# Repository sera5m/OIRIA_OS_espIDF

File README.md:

# OIRIA OS (ESP-IDF)

Smartwatch firmware. Dual purpose: a normal smart device, and an industrial or semi-universal controller for whatever hardware it meets — consumer gear, raw modules, or robotics, all in one device.

## what

OIRIA OS is intended to behave like Linux for small devices that have no MMU, without containing any Linux components. It should be friendly enough for a layman and deep enough for an expert, with a clean path between the two. It is also meant to meet high performance criteria for microcontrollers.

The smartlink companion is part of this, given The watch is both a wearable and a controller.

## why

Wear OS is not good enough. Many standard libraries (microGL and the like) do not meet the performance bar. Mixed drivers and manufacturers rarely work together because of side effects, nonstandard management, or nonstandard I/O state machines. A small, owned stack avoids that.

## how

OIRIA OS is broken into state-machine layers with component managers, similar to how modern Linux handles services. Encapsulation is kept thin for performance. There is no user/kernel boundary and no MMU sandbox. Isolation is by convention and by declared capabilities. FreeRTOS sits under everything. Two long-lived managers (WindowManager and appManager) own the frame and the app list. Apps own their windows. Input is handled by asynch events with periodic check. ipc is handled by rshell pipes as a DataItem when it needs to leave an app, or the device itself (best performance with batching; low latency without, but higher overhead)

---

# Main services

**graphics system**

- name: WindowManager (`os_code/core/window_env/MWenv`)
- purpose: display compositor. Owns the window list, z-order, and the frame. Draws windows to the framebuffer and pushes dirty rows to the panel.
- architectural principles: apps build a `Window` and hand it to the manager. The manager borrows; it does not own the content. Dirty flags over full redraws. Double-buffered framebuffer, 45 fps cap. Style and widgets live in `window_env/ui`. DOM pack exists for the second chip; apply-to-LCD is not wired yet.

**desktop environment**

- name: apps + appManager focus
- purpose: the set of things the user sees and switches between (menu, watch face, health, browser, and so on). Focus is a pointer plus a highlight flag plus a layer number.
- architectural principles: an app is not a system object that requests a window. It constructs one. `set_focused_app` raises the window and sets the highlight. The input path delivers events only to the focused app. No desktop shell in the Unix sense — the menu and the focused app are the desktop.

**input system**

- name: input handler (`os_code/middle_layer/input`)
- purpose: turn hardware (encoder knobs, buttons, and later USB HID) into `InputEvent`s and route them.
- architectural principles: one packed event, one queue (`ProcInputQueTarget`). The input task produces; apps consume via `receive_event_input`. No device-node tree. Target enum decides where it goes. Keyboard, mouse, touch, and phone-as-input are not in the path yet.

**application scheduler and system**

- name: rshell (`os_code/core/rShell`)
- purpose: app lifecycle and scheduling on top of FreeRTOS. Registers apps, opens them, starts their task, routes input and pipes, and owns focus.
- architectural principles: `AppBase` is the unit. `start_task` is an `xTaskCreate` of a loop that calls `tick_app` at `tick_rate_hz` and feeds the watchdog. Input arrives on a separate path (`route_input_to_focused`). Pipes and DataItems are the long-term data currency; most apps still talk to their window directly. Capabilities are declared on the manifest (`USES_SD_CARD`, `STREAM_OUT_CAPABLE`, and others) and checked at the call for GPIO, wireless, and wake. The ELF loader is not sandboxed (no mmu) so be careful if developing. further suppoer will be added in the future

**scripting**

- name: Toplethos (`os_code/core/rs_vm`)
- purpose: on-device scripting layer for behavior that does not belong in C++.
- architectural principles: bytecode interpreter (`rsvm_compile` + `rsvm_run`). No JIT on the ESP32-S3. The VM asks the host through function pointers; the host is not a kernel. Desktop AOT and the full language tree live elsewhere, as this device can only handle a small subset of features and will not be able to handle simd, self modifying code, intelegently self modifying code, or high bit width instructions or workloads)
why: bash is too simple. lua slow and big. java too huge and does not allow manual memory access. 

---

**Build:** this repo is the ESP-IDF project. See [BUILD.md](BUILD.md).

```bash
. ~/esp/esp-idf/export.sh
git clone https://github.com/sera5m/OIRIA_OS_espIDF
cd OIRIA_OS_espIDF
idf.py build
idf.py -p /dev/ttyACM0 flash monitor

```
**developing apps for this device**
app development is still experimental and desktop-only. support coming to the mobile app sometime in the future. please test all of your apps features before submitting it to the repo [HERE](https://github.com/sera5m/oiria-index)

**SMARTLINK APP**
[MOBILE, ANDROID](https://github.com/sera5m/android_smartlink_app)
[mobile, apple] (lol)
[DESKTOP, LINUX,arch x86] (NOT DONE) 
[DESKTOP, LINUX, deb] (not done)
[DESKTOP, microslop windows] (not done)

**LIABILITY WARNING**
this device is still experimental and may not perform exactly as indented, this being an inherent limitation of software. while the creators of this software have taken all caution to maintain legality and safety in features, this device is a tool, and as with all tools, misuse is possible. ensure that the electronics toolkit, universal remote, or quick utils are used only on devices that you have ownership of

**WARNING**

This device uses a custom programming language named **Toplethos** as a scripting layer, for more detailed behavior and edge programming than bash or Lua. It is a C++/Rust-like language with several features inspired by Lisp. It can be interpreted (full support for a RISC-like 32-bit subset) and compiled on device (support incomplete — file bug reports, as unexpected behavior will occur; Xtensa LX7 is not fully documented, with mixed registers, bit width, and register rotation that do not behave like standard ARM or RISC-V).

Toplethos on the watch is `os_code/core/rs_vm/` (compiled in). The desktop/reference tree is separate and **not** required to flash:

**https://github.com/sera5m/toplethos-lang**

```bash
git submodule update --init --recursive   # optional, fills third_party/toplethos-lang
```

See `readme.md` for the longer manual page, plus `TOPLETHOS.md`, `SIGGEN.md`, `BUILD.md`.

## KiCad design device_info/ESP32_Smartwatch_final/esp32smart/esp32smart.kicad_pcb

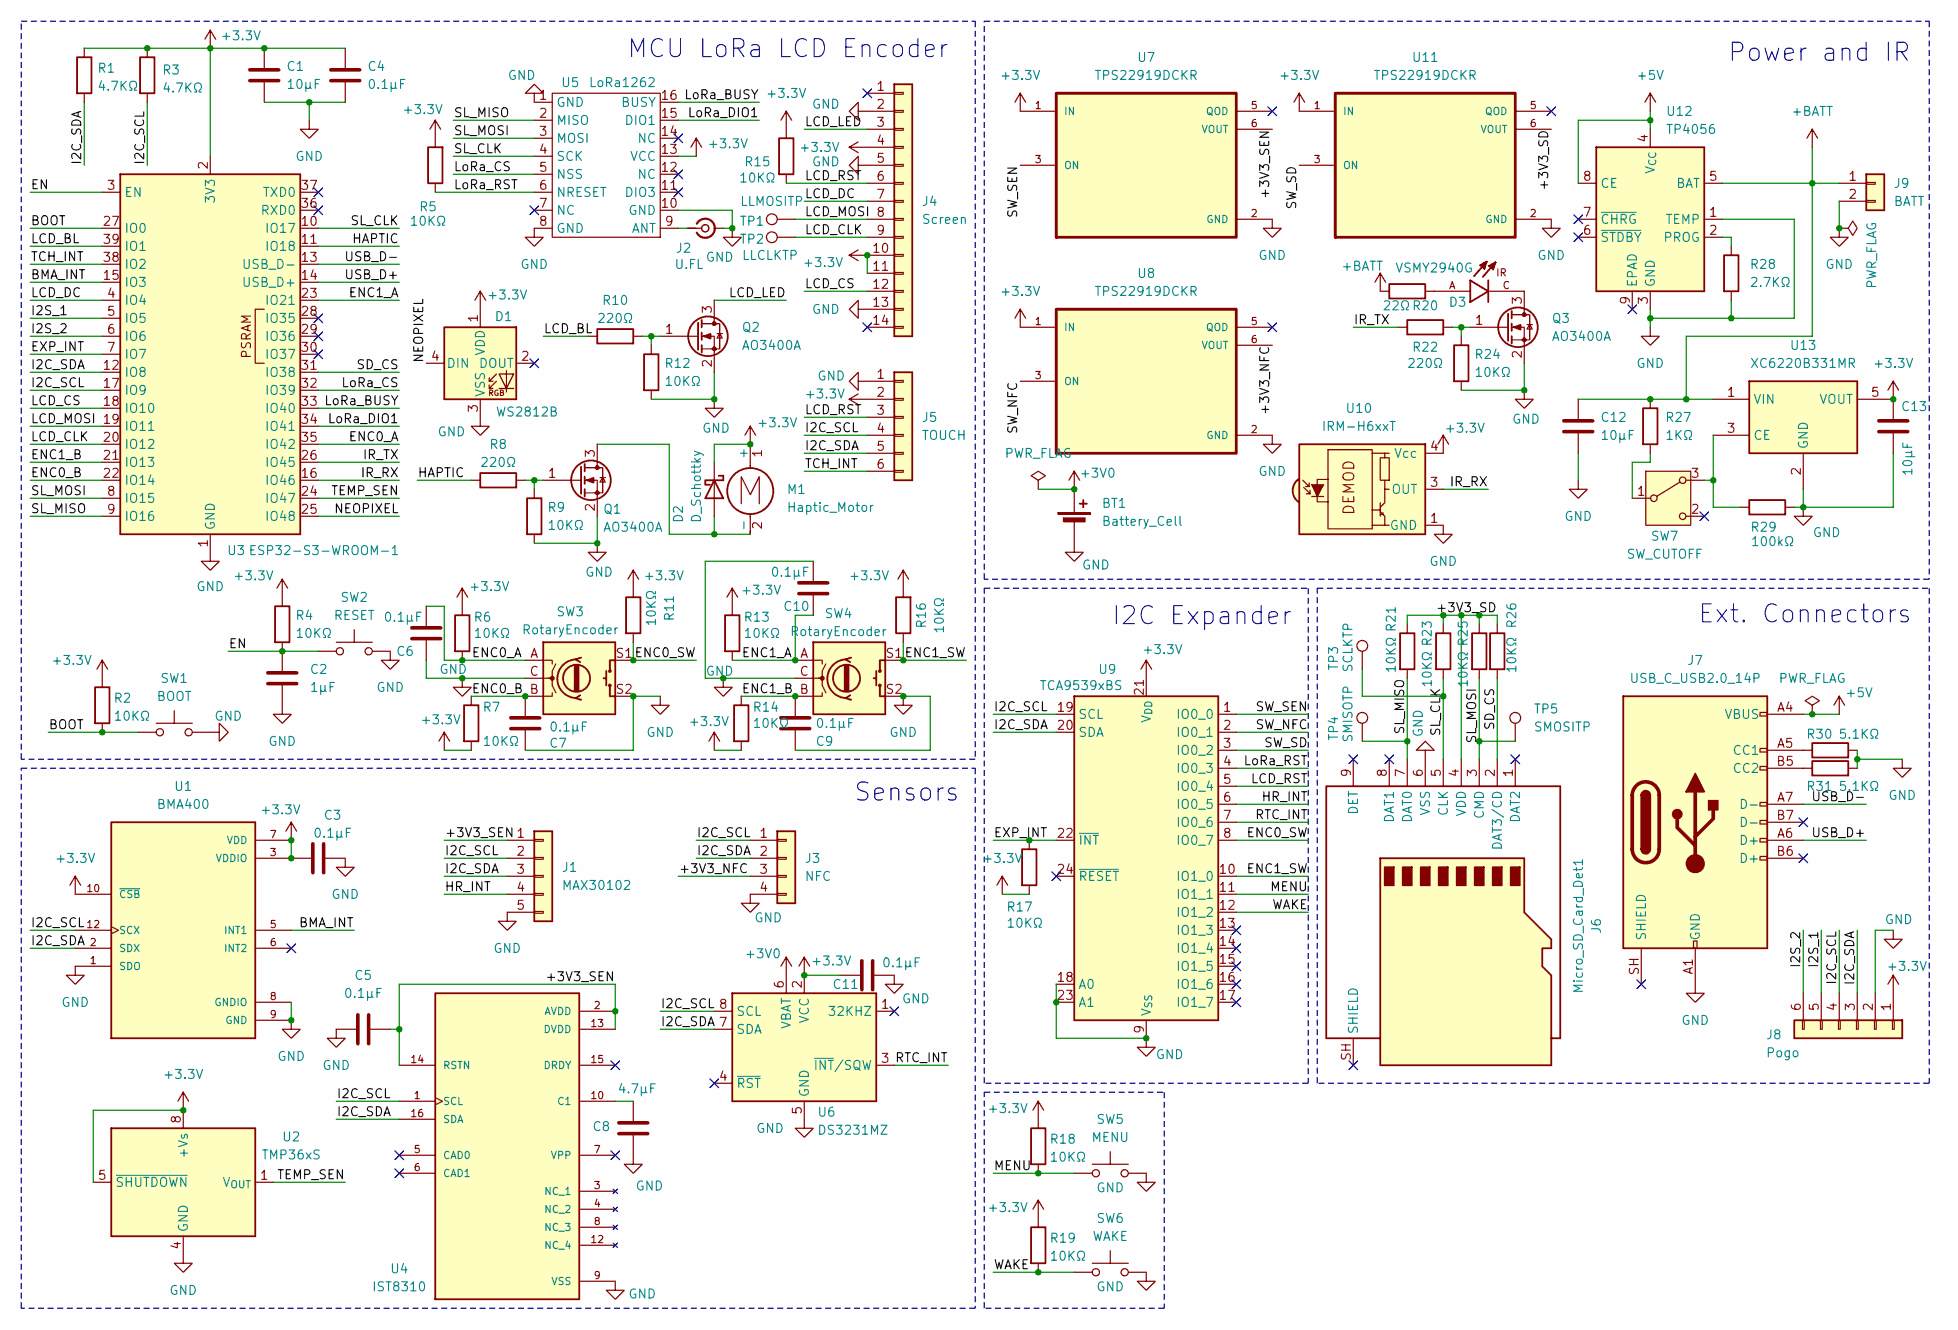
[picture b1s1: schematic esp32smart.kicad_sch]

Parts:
BT1: Battery_Cell; BatteryHolder_Seiko_MS621F
C1, C12, C13: 10μF; C_0603_1608Metric
C2: 1µF; C_0402_1005Metric
C3, C5, C6, C7, C9, C10, C11: 0.1µF; C_0402_1005Metric
C4: 0.1μF; C_0402_1005Metric
C8: 4.7µF; C_0603_1608Metric
D1: WS2812B; LED_WS2812B_PLCC4_5.0x5.0mm_P3.2mm
D2: D_Schottky; D_0603_1608Metric
D3: VSMY2940G; LED_0805_2012Metric; PARTREV 1.1
J1: MAX30102; PinHeader_1x05_P1.27mm_Vertical
J2: U.FL; U.FL_Hirose_U.FL-R-SMT-1_Vertical
J3: NFC; PinHeader_1x04_P1.27mm_Vertical
J4: Screen; Hirose_FH12-14S-0.5SH_1x14-1MP_P0.50mm_Horizontal
J5: TOUCH; Hirose_FH12-6S-0.5SH_1x06-1MP_P0.50mm_Horizontal
J6: Micro_SD_Card_Det1; microSD_HC_Hirose_DM3AT-SF-PEJM5
J7: USB_C_USB2.0_14P; USB_C_Receptacle_HRO_TYPE-C-31-M-12
J8: Pogo; PinHeader_1x06_P2.54mm_Vertical
J9: BATT; JST_SH_SM02B-SRSS-TB_1x02-1MP_P1.00mm_Horizontal
M1: Haptic_Motor; PinHeader_1x02_P1.27mm_Vertical
Q1, Q2, Q3: AO3400A; SOT-23
R1, R3: 4.7KΩ; R_0402_1005Metric
R2, R4, R5, R6, R7, R9, R11, R12, R13, R14, R15, R16, R17, R18, R19, R21, R23, R24, R25, R26: 10KΩ; R_0402_1005Metric
R8, R10, R22: 220Ω; R_0402_1005Metric
R20: 22Ω; R_0402_1005Metric
R27: 1KΩ; R_0402_1005Metric
R28: 2.7KΩ; R_0402_1005Metric
R29: 100kΩ; R_0402_1005Metric
R30, R31: 5.1KΩ; R_0402_1005Metric
SW1: BOOT; SW_SPST_B3U-3000P
SW2: RESET; SW_SPST_B3U-3000P
SW3, SW4: RotaryEncoder; EC04_TerwinSW
SW5: MENU; SW_SPST_B3U-3000P
SW6: WAKE; SW_SPST_B3U-3000P
SW7: SW_CUTOFF; SW_Slide-03_Wuerth-WS-SLTV_10x2.5x6.4_P2.54mm
TP1: LLMOSITP; TestPoint_Pad_D1.0mm
TP2: LLCLKTP; TestPoint_Pad_D1.0mm
TP3: SCLKTP; TestPoint_Pad_D1.0mm
TP4: SMISOTP; TestPoint_Pad_D1.0mm
TP5: SMOSITP; TestPoint_Pad_D1.0mm
U1: BMA400; LGA-12_2x2mm_P0.5mm
U2: TMP36xS; SOIC-8_3.9x4.9mm_P1.27mm
U3: ESP32-S3-WROOM-1
U4: IST8310; QFN-16-1EP_3x3mm_P0.5mm_EP1.7x1.7mm; PARTREV 1.4
U5: LoRa1262
U6: DS3231MZ; SOIC-8_3.9x4.9mm_P1.27mm
U7, U8, U11: TPS22919DCKR; SOT-363_SC-70-6
U9: TCA9539xBS; HVQFN-24-1EP_4x4mm_P0.5mm_EP2.1x2.1mm
U10: IRM-H6xxT; Everlight_IRM-H6xxT
U12: TP4056; SOIC-8-1EP_3.9x4.9mm_P1.27mm_EP2.41x3.3mm_ThermalVias
U13: XC6220B331MR; SOT-23-5

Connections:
+3.3V: C1.1, C3.2, C4.1, C11.1, C13.1, D1.1 (VDD), D2.1 (K), J4.4, J4.10, J4.11, J5.2, J8.1, M1.1 (+), R1.1, R2.1, R3.1, R4.1, R5.2, R6.1, R7.2, R11.1, R13.1, R14.2, R15.1, R16.2, R17.2, R18.1, R19.1, U1.3 (VDDIO), U1.7 (VDD), U1.10 (~CSB), U2.5 (~SHUTDOWN), U2.8 (+Vs), U3.2 (3V3), U5.13 (VCC), U6.2 (VCC), U7.1 (IN), U8.1 (IN), U9.21 (V_{DD}), U10.4 (Vcc), U11.1 (IN), U13.5 (VOUT)
+3V0: BT1.1 (+), U6.6 (VBAT)
+5V: J7.A4 (VBUS), J7.A9 (VBUS), J7.B4 (VBUS), J7.B9 (VBUS), U12.4 (V_{CC}), U12.8 (CE)
+BATT: C12.1, J9.1, R20.1, R27.1, U12.5 (BAT), U13.1 (VIN)
/+3V3_NFC: J3.3, U8.6 (VOUT)
/+3V3_SD: J6.4 (VDD), R21.1, R23.1, R25.1, R26.1, U11.6 (VOUT)
/+3V3_SEN: C5.2, J1.1, U4.2 (AVDD), U4.13 (DVDD), U4.14 (RSTN), U7.6 (VOUT)
/BMA_INT: U1.5 (INT1), U3.15 (IO3)
/BOOT: R2.2, SW1.1, U3.27 (IO0)
/EN: C2.1, R4.2, SW2.1, U3.3 (EN)
/ENC0_A: C6.1, R6.2, SW3.A, U3.35 (IO42)
/ENC0_B: C7.1, R7.1, SW3.B, U3.22 (IO14)
/ENC0_SW: R11.2, SW3.S1, U9.8 (IO0_7)
/ENC1_A: C10.2, R13.2, SW4.A, U3.23 (IO21)
/ENC1_B: C9.1, R14.1, SW4.B, U3.21 (IO13)
/ENC1_SW: R16.1, SW4.S1, U9.10 (IO1_0)
/EXP_INT: R17.1, U3.7 (IO7), U9.22 (~INT)
/HAPTIC: R8.1, U3.11 (IO18)
/HR_INT: J1.4, U9.6 (IO0_5)
/I2C_SCL: J1.2, J3.1, J5.4, J8.4, R3.2, U1.12 (SCX), U3.17 (IO9), U4.1 (SCL), U6.8 (SCL), U9.19 (SCL)
/I2C_SDA: J1.3, J3.2, J5.5, J8.3, R1.2, U1.2 (SDX), U3.12 (IO8), U4.16 (SDA), U6.7 (SDA), U9.20 (SDA)
/I2S_1: J8.5, U3.5 (IO5)
/I2S_2: J8.6, U3.6 (IO6)
/IR_RX: U3.16 (IO46), U10.3 (OUT)
/IR_TX: R22.1, U3.26 (IO45)
/LCD_BL: R10.1, U3.39 (IO1)
/LCD_CLK: J4.9, TP2.1 (1_1), U3.20 (IO12)
/LCD_CS: J4.12, U3.18 (IO10)
/LCD_DC: J4.7, U3.4 (IO4)
/LCD_LED: J4.3, Q2.3 (D)
/LCD_MOSI: J4.8, TP1.1 (1_1), U3.19 (IO11)
/LCD_RST: J4.6, J5.3, R15.2, U9.5 (IO0_4)
/LoRa_BUSY: U3.33 (IO40), U5.16 (BUSY)
/LoRa_CS: U3.32 (IO39), U5.5 (NSS)
/LoRa_DIO1: U3.34 (IO41), U5.15 (DIO1)
/LoRa_RST: R5.1, U5.6 (NRESET), U9.4 (IO0_3)
/MENU: R18.2, SW5.1, U9.11 (IO1_1)
/NEOPIXEL: D1.4 (DIN), U3.25 (IO48)
/RTC_INT: U6.3 (~INT/SQW), U9.7 (IO0_6)
/SD_CS: J6.2 (DAT3/CD), R26.2, U3.31 (IO38)
/SL_CLK: J6.5 (CLK), R23.2, TP3.1 (1_1), U3.10 (IO17), U5.4 (SCK)
/SL_MISO: J6.7 (DAT0), R21.2, TP4.1 (1_1), U3.9 (IO16), U5.2 (MISO)
/SL_MOSI: J6.3 (CMD), R25.2, TP5.1 (1_1), U3.8 (IO15), U5.3 (MOSI)
/SW_NFC: U8.3 (ON), U9.2 (IO0_1)
/SW_SD: U9.3 (IO0_2), U11.3 (ON)
/SW_SEN: U7.3 (ON), U9.1 (IO0_0)
/TCH_INT: J5.6, U3.38 (IO2)
/TEMP_SEN: U2.1 (V_{OUT}), U3.24 (IO47)
/USB_D+: J7.A6 (D+), U3.14 (USB_D+)
/USB_D-: J7.A7 (D-), U3.13 (USB_D-)
/WAKE: R19.2, SW6.1, U9.12 (IO1_2)
GND: BT1.2 (-), C1.2, C2.2, C3.1, C4.2, C5.1, C6.2, C7.2, C8.2, C9.2, C10.1, C11.2, C12.2, C13.2, D1.3 (VSS), J1.5, J2.2 (Ext), J3.4, J4.2, J4.5, J4.13, J5.1, J6.6 (VSS), J7.A1 (GND), J7.A12 (GND), J7.B1 (GND), J7.B12 (GND), J8.2, J9.2, Q1.2 (S), Q2.2 (S), Q3.2 (S), R9.2, R12.2, R24.2, R28.2, R29.2, R30.2, R31.2, SW1.2, SW2.2, SW3.C, SW3.S2, SW4.C, SW4.S2, SW5.2, SW6.2, U1.1 (SDO), U1.8 (GNDIO), U1.9 (GND), U2.4 (GND), U3.1 (GND), U3.40 (GND), U3.41 (GND), U4.9 (VSS), U4.11 (VSS), U5.1 (GND), U5.8 (GND), U5.10 (GND), U6.5 (GND), U7.2 (GND), U8.2 (GND), U9.9 (V_{SS}), U9.18 (A0), U9.23 (A1), U9.25 (V_{SS}), U10.1 (GND), U10.2 (GND), U11.2 (GND), U12.1 (TEMP), U12.3 (GND), U13.2 (GND)
unnamed: D2.2 (A), M1.2 (-), Q1.3 (D)
unnamed: D3.A, R20.2
unnamed: J2.1 (In), U5.9 (ANT)
unnamed: J7.A5 (CC1), R30.1
unnamed: J7.B5 (CC2), R31.1
unnamed: Q1.1 (G), R8.2, R9.1
unnamed: Q2.1 (G), R10.2, R12.1
unnamed: D3.C, Q3.3 (D)
unnamed: Q3.1 (G), R22.2, R24.1
unnamed: R29.1, SW7.3 (A), U13.3 (CE)
unnamed: R27.2, SW7.1 (B)
unnamed: C8.1, U4.10 (C1)
unnamed: R28.1, U12.2 (PROG)

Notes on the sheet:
MCU LoRa LCD Encoder
Ext. Connectors
Power and IR
Sensors
I2C Expander

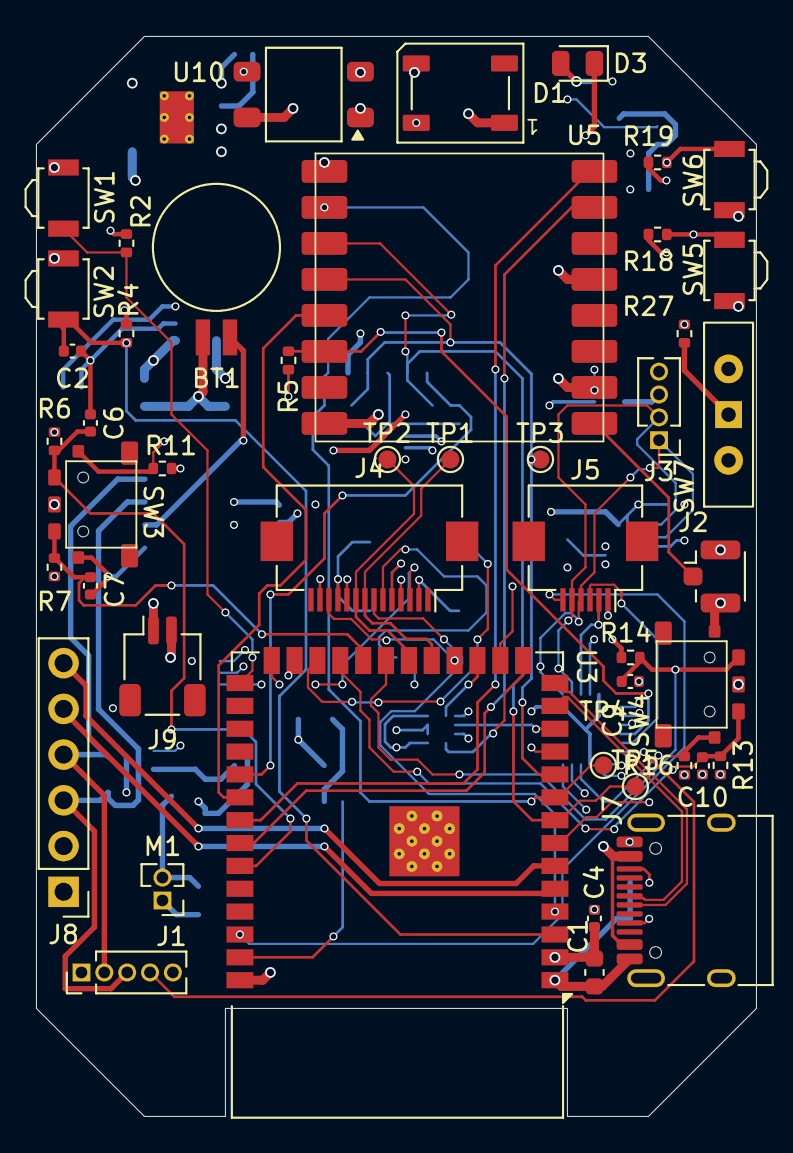
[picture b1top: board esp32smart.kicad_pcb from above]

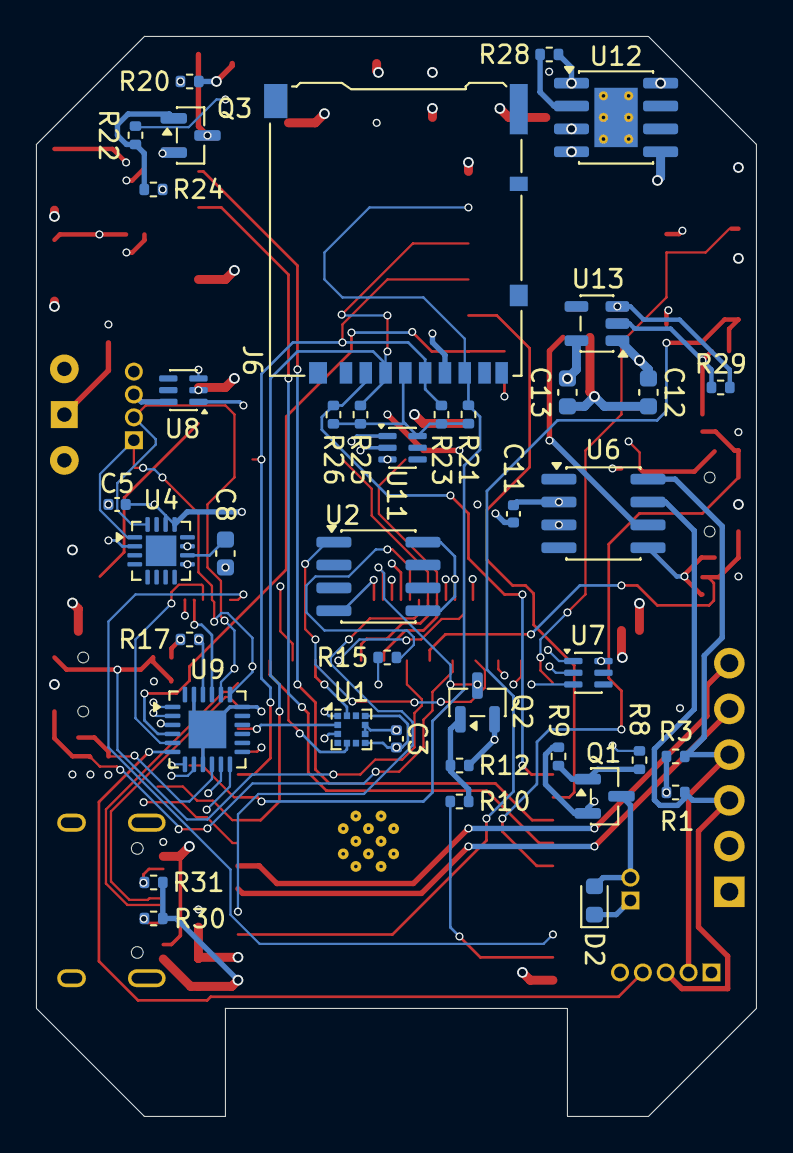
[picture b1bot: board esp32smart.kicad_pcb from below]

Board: 4 copper layers, 40.0 x 60.0 mm, 86 parts (40 on the bottom side), 65 nets.

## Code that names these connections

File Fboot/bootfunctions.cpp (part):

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{
    if (enable) {
        gpio_config_t io = {
            .pin_bit_mask = (1ULL << LCD_DC) | (1ULL << LCD_RST) | (1ULL << lcd_BL),
            .mode = GPIO_MODE_OUTPUT,
        };
        ESP_ERROR_CHECK(gpio_config(&io));

        gpio_set_direction(SPI_CS_LCD, GPIO_MODE_OUTPUT);
        gpio_set_level(SPI_CS_LCD, 1);
        gpio_set_level(LCD_RST, 1);
        gpio_set_level(LCD_DC, 0);
        gpio_set_level(lcd_BL, 1);
    } else {
        gpio_reset_pin(LCD_DC);
        gpio_reset_pin(LCD_RST);
        gpio_reset_pin(lcd_BL);
        gpio_reset_pin(SPI_CS_LCD);
    }
    return ESP_OK;
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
